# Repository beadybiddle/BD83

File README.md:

# BD83
A fully custom 83 Key mechanical keyboard designed around the way that I type. I intend to be able to say that this is truly a keyboard customized to my liking.
The original motivation behind this project was just a frustration at standard ANSI layouts. This project features custom everything, including PCB, plate, case, firmware, and eventually keycaps. Before creating anything, I initially just filmed my hands typing and gaming for an hour to figure out my own tendencies and key usage.

### Layout changes:
- Space bar is shrunk and split because nobody needs six keys' worth of real estate to hit one button.
- Backspace is shrunk because I don't intend to use it there. I've added a secondary backspace between the space bars.
- Caps lock is useless. I've removed it.
- Right shift is useless. I've removed it.
- Numpad function is incorporated into the FN layer on the lefthand side.
- Nav cluster has been moved around the arrow keys so it's easier and more intuitive to navigate code with home/end.
- F13 is now a thing because I had room for it.

### Hardware
There are three main custom hardware components to this keyboard:
- PCB, self explanatory
- Plate, the layer that the keyswitches clip into
- Case, the pieces that house the rest of the board

#### Plate
Keyboards don't necessarily need a plate, but for a myriad of reasons it made sense for me to use one. The plate is 0.06" 304 stainless steel, making it unyielding which is better for linear switch typefeel. I generated a template in swillKB then modeled the plate in Fusion360. Using the DXF exported from Fusion, I waterjet cut the plate.

#### Case
I've designed two cases, one which is full-sized and intended to be printed on a Form 3L SLA printer at the GaTech Invention Studio, and another which is minimal (hardly qualifying as a case) that I printed on my Voxelab Aquila. All outward-facing edges are chamfered or filleted to look nice and not hurt the flesh. On the back is a hole for a USB-C adapter dongle to poke through. The underside features a pretty beadybiddle logo and some rubber feet made from EPDM rubber bands. I also designed a wrist rest to be extra, but I've made the case so slim that it's not necessary.
I was unable to get access to the Form 3L before the studio closed for the year.

The two halves of the case are fastened by eight M3x10 machine screws and nuts around the perimeter. The plate has flanges around the edges that allow it to be sandwiched between these two halves, cushioned by strips of EPDM to dampen the sound and make the typefeel just a little springy. The interior of the case has only 0.8mm of wiggle room to the dangling PCB, making it literally as compact as possible. It is angled five degrees so that the front height is minimized while making room for the Feather board and batteries in the back.

The minimal "case" is actually four feet that clip onto the plate and are secured by a single large band. It has the same five degree inclination as the full case so that the electronics won't touch the desk surface. The open design leaves the switches and PCB accessible.

#### PCB
The PCB took the longest of all the components (maybe because I'd never made one before) but I'll try to keep it brief here:
I made it to support three main features: bluetooth, RGB lighting, and some level of expandability.
The brains of the board is an Adafruit Feather 32u4 Bluefruit LE, which is a devboard with an intregated nRF51822 BLE module. It also handles LiPo power for going completely wireless.
The LEDs are common-anode RGB packages, and are controlled by two IS31FL3733B drivers. The MCU talks to these drivers via I2C. I was originally planning to use a string of WS2812Bs or SK6812Es, but these have a substantially higher power draw than the ISSI scanning matrix drivers.
There are only 20 GPIO pins on the Feather, though, and several are already used for SPI with the BLE module. In order to accomodate my ideal 83 keys, it would take at least 19 pins to connect all the switches even with matrix duplexing, a number that I couldn't muster while dedicating three to the LED drivers. To get get some extra GPIO, I use an MCP23017 I2C I/O expander. This communicates on the same I2C lines as the ISSI drivers, and creates an additional 16 GPIO pins - more than enough for the rest of the switch matrix.

Diodes are placed between each switch and its corresponding row to prevent ghosting as the matrix is scanned.
VCC is fed through decoupling caps as needed to the slave chips; decoupling around the MCU is already handled by the Feather board.
The address pins on the three I2C chips have solder bridges for customizing the addresses if more devices are added.
A SPDT switch controls the 3V3 regulator enable pin so that power can be controlled, especially when going wireless.

The PCB was definitely the most fun part of this whole project; learning to make something so different from what I'm used to was nice.
I routed all of the traces twice because after getting an understanding and making some messy paths the first time it was much easier to organize the rats nest from scratch.
I also went through several iterations of component placements in the process in order to make room for the traces and switches. Most keyboards have plenty of free real estate behind their big spacebars or above the arrow keys, but my compact layout meant everything had to be crammed in tight gaps.

This was also the first time I'd done reflow soldering, but that was easy enough with the stencil and oven. And only one diode was backwards!

Designed in KiCad and fabricated by JLCPCB.

### Firmware
Easily the most difficult (or maybe just frustrating?) part, I wrote custom firmware for the board with the help of the QMK framework. QMK handles a lot of the nitty gritty stuff so that I instead dedicate dozens of hours to custom matrix scanning and debugging the RGB.
Defining switch order, keymappings, and LED positions was tedious but simple. The real problem was that as far as I can tell, I'm the first person to make a keyboard that drives rows from the MCU and read columns from an IO expander.
I visited square one a few times, rewriting the firmware each time I ran into a deadend that couldn't be debugged.
The first time, I thought the board wasn't flashing. Turns out it was flashing, but the firmware I wrote sucked so bad that it kicked back into bootloader.
The second time, I had it flashed but nothing responded and no debug messages even printed. I never figured out why, because I just rewrote everything after a day of failed debugging.
Finally I have the (mostly) working firmware, which is fully functional as a keyboard input and also supports typing over bluetooth. Unfortunately the RGB still doesn't work for some unknown reason, but luckily the BLE meets the critera for additional features to the keyboard.

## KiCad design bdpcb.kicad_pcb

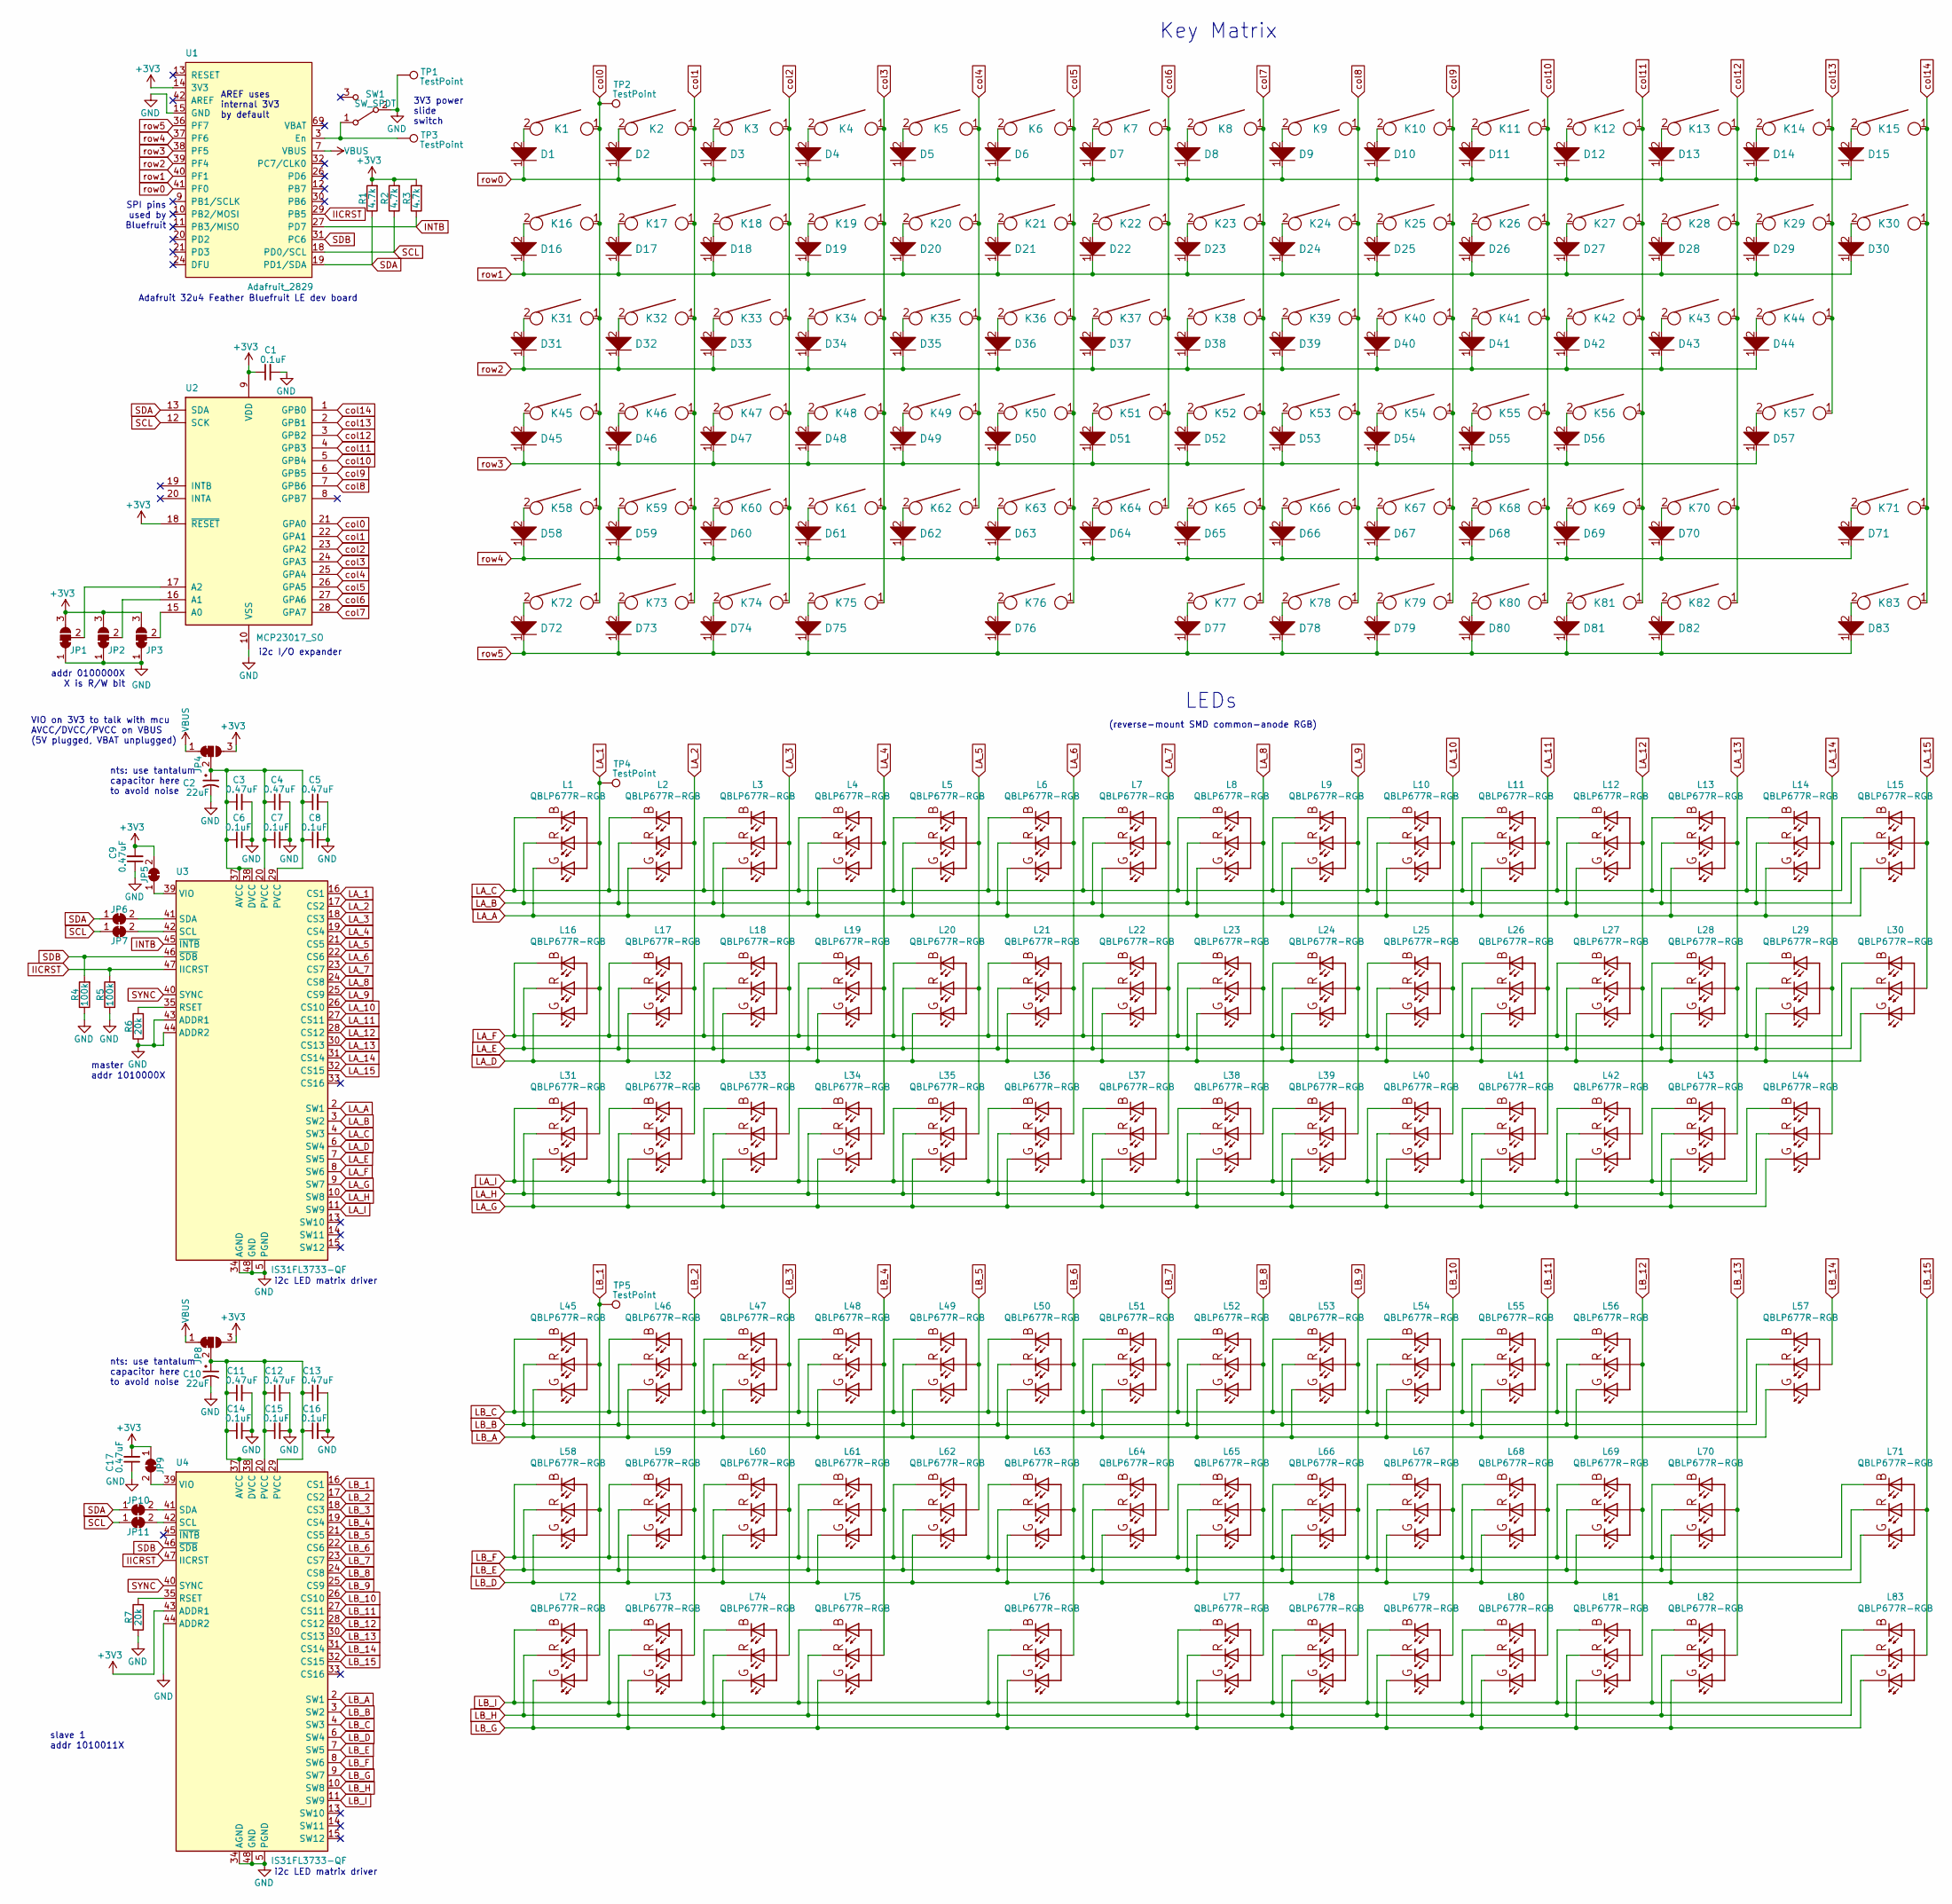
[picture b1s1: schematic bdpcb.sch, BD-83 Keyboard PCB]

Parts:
C1, C6, C7, C8, C14, C15, C16: 0.1uF; C_0805_2012Metric
C2, C10: 22uF; C_0805_2012Metric
C3, C4, C5, C9, C11, C12, C13, C17: 0.47uF; C_0805_2012Metric
D1, D2, D3, D4, D5, D6, D7, D8, D9, D10, D11, D12, D13, D14, D15, D16, D17, D18, D19, D20, D21, D22, D23, D24, D25, D26, D27, D28, D29, D30, D31, D32, D33, D34, D35, D36, D37, D38, D39, D40, D41, D42, D43, D44, D45, D46, D47, D48, D49, D50, D51, D52, D53, D54, D55, D56, D57, D58, D59, D60, D61, D62, D63, D64, D65, D66, D67, D68, D69, D70, D71, D72, D73, D74, D75, D76, D77, D78, D79, D80, D81, D82, D83: D; D_SOD-123
JP1, JP2, JP3, JP4, JP8: 13_bridge; SolderJumper-3_P1.3mm_Bridged12_RoundedPad1.0x1.5mm
JP5, JP6, JP7, JP9, JP10, JP11: SolderJumper_2_Bridged; SolderJumper-2_P1.3mm_Bridged_RoundedPad1.0x1.5mm
K1, K2, K3, K4, K5, K6, K7, K8, K9, K10, K11, K12, K13, K14, K15, K16, K17, K18, K19, K20, K21, K22, K23, K24, K25, K26, K27, K28, K29, K30, K32, K33, K34, K35, K36, K37, K38, K39, K40, K41, K42, K43, K46, K47, K48, K49, K50, K51, K52, K53, K54, K55, K56, K59, K60, K61, K62, K63, K64, K65, K66, K67, K68, K69, K70, K71, K76, K78, K79, K80, K81, K82, K83: KEYSW; MXOnly-1U-NoLED
K31, K44: KEYSW; MXOnly-1.5U-NoLED
K45: KEYSW; MXOnly-1.75U-NoLED
K57: KEYSW; MXOnly-2.25U-NoLED
K58: KEYSW; MXOnly-2U-NoLED
K72, K73, K74: KEYSW; MXOnly-1.25U-NoLED
K75, K77: KEYSW; MXOnly-2U-ReversedStabilizers-NoLED
L1, L2, L3, L4, L5, L6, L7, L8, L9, L10, L11, L12, L13, L14, L15, L16, L17, L18, L19, L20, L21, L22, L23, L24, L25, L26, L27, L28, L29, L30, L31, L32, L33, L34, L35, L36, L37, L38, L39, L40, L41, L42, L43, L44, L45, L46, L47, L48, L49, L50, L51, L52, L53, L54, L55, L56, L57, L58, L59, L60, L61, L62, L63, L64, L65, L66, L67, L68, L69, L70, L71, L72, L73, L74, L75, L76, L77, L78, L79, L80, L81, L82, L83: QBLP677R-RGB; RGB-REVERSE_MOUNT
R1, R2, R3: 4.7k; R_0805_2012Metric
R4, R5: 100k; R_0805_2012Metric
R6, R7: 20k; R_0805_2012Metric
SW1: SW_SPDT; SW_SPDT_CK-JS102011SAQN
TP1, TP3: TestPoint; TestPoint_Plated_Hole_D2.0mm
TP2, TP4, TP5: TestPoint; TestPoint_Pad_D2.5mm
U1: Adafruit_2829; ADAFRUIT_2829
U2: MCP23017_SO; SOIC-28W_7.5x17.9mm_P1.27mm
U3, U4: IS31FL3733-QF; QFN-48-1EP_6x6mm_P0.4mm_EP4.2x4.2mm

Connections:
+3V3: C1.1, C9.2, C17.2, JP1.3 (B), JP2.3 (B), JP3.3 (B), JP4.3 (B), JP5.2 (B), JP8.3 (B), JP9.1 (A), R1.2, R2.2, R3.2, U1.14 (3V3), U2.9 (VDD), U2.18 (~RESET~), U4.43 (ADDR1); also elsewhere on the board
GND: C1.2, C2.2, C3.2, C4.2, C5.2, C6.2, C7.2, C8.2, C9.1, C10.2, C11.2, C12.2, C13.2, C14.2, C15.2, C16.2, C17.1, JP1.1 (A), JP2.1 (A), JP3.1 (A), R4.1, R5.1, R6.1, R7.1, SW1.2 (B), TP1.1, U1.15 (GND), U2.10 (VSS), U3.5 (PGND), U3.12 (PGND), U3.34 (AGND), U3.43 (ADDR1), U3.44 (ADDR2), U3.48 (GND), U3.49 (GND), U4.5 (PGND), U4.12 (PGND), U4.34 (AGND), U4.44 (ADDR2), U4.48 (GND), U4.49 (GND)
IICRST: R5.2, U1.29 (PB5), U3.47 (IICRST), U4.47 (IICRST)
INTB: R3.1, U1.27 (PD7), U3.45 (~INTB)
LA_1: L1.COMMON_ANODE, L16.COMMON_ANODE, L31.COMMON_ANODE, TP4.1, U3.16 (CS1)
LA_2: L2.COMMON_ANODE, L17.COMMON_ANODE, L32.COMMON_ANODE, U3.17 (CS2)
LA_3: L3.COMMON_ANODE, L18.COMMON_ANODE, L33.COMMON_ANODE, U3.18 (CS3)
LA_4: L4.COMMON_ANODE, L19.COMMON_ANODE, L34.COMMON_ANODE, U3.19 (CS4)
LA_5: L5.COMMON_ANODE, L20.COMMON_ANODE, L35.COMMON_ANODE, U3.21 (CS5)
LA_6: L6.COMMON_ANODE, L21.COMMON_ANODE, L36.COMMON_ANODE, U3.22 (CS6)
LA_7: L7.COMMON_ANODE, L22.COMMON_ANODE, L37.COMMON_ANODE, U3.23 (CS7)
LA_8: L8.COMMON_ANODE, L23.COMMON_ANODE, L38.COMMON_ANODE, U3.24 (CS8)
LA_9: L9.COMMON_ANODE, L24.COMMON_ANODE, L39.COMMON_ANODE, U3.25 (CS9)
LA_10: L10.COMMON_ANODE, L25.COMMON_ANODE, L40.COMMON_ANODE, U3.26 (CS10)
LA_11: L11.COMMON_ANODE, L26.COMMON_ANODE, L41.COMMON_ANODE, U3.27 (CS11)
LA_12: L12.COMMON_ANODE, L27.COMMON_ANODE, L42.COMMON_ANODE, U3.28 (CS12)
LA_13: L13.COMMON_ANODE, L28.COMMON_ANODE, L43.COMMON_ANODE, U3.30 (CS13)
LA_14: L14.COMMON_ANODE, L29.COMMON_ANODE, L44.COMMON_ANODE, U3.31 (CS14)
LA_15: L15.COMMON_ANODE, L30.COMMON_ANODE, U3.32 (CS15)
LA_A: L1.2, L2.2, L3.2, L4.2, L5.2, L6.2, L7.2, L8.2, L9.2, L10.2, L11.2, L12.2, L13.2, L14.2, L15.2, U3.2 (SW1)
LA_B: L1.3, L2.3, L3.3, L4.3, L5.3, L6.3, L7.3, L8.3, L9.3, L10.3, L11.3, L12.3, L13.3, L14.3, L15.3, U3.3 (SW2)
LA_C: L1.1, L2.1, L3.1, L4.1, L5.1, L6.1, L7.1, L8.1, L9.1, L10.1, L11.1, L12.1, L13.1, L14.1, L15.1, U3.4 (SW3)
LA_D: L16.2, L17.2, L18.2, L19.2, L20.2, L21.2, L22.2, L23.2, L24.2, L25.2, L26.2, L27.2, L28.2, L29.2, L30.2, U3.6 (SW4)
LA_E: L16.3, L17.3, L18.3, L19.3, L20.3, L21.3, L22.3, L23.3, L24.3, L25.3, L26.3, L27.3, L28.3, L29.3, L30.3, U3.7 (SW5)
LA_F: L16.1, L17.1, L18.1, L19.1, L20.1, L21.1, L22.1, L23.1, L24.1, L25.1, L26.1, L27.1, L28.1, L29.1, L30.1, U3.8 (SW6)
LA_G: L31.2, L32.2, L33.2, L34.2, L35.2, L36.2, L37.2, L38.2, L39.2, L40.2, L41.2, L42.2, L43.2, L44.2, U3.9 (SW7)
LA_H: L31.3, L32.3, L33.3, L34.3, L35.3, L36.3, L37.3, L38.3, L39.3, L40.3, L41.3, L42.3, L43.3, L44.3, U3.10 (SW8)
LA_I: L31.1, L32.1, L33.1, L34.1, L35.1, L36.1, L37.1, L38.1, L39.1, L40.1, L41.1, L42.1, L43.1, L44.1, U3.11 (SW9)
LB_1: L45.COMMON_ANODE, L58.COMMON_ANODE, L72.COMMON_ANODE, TP5.1, U4.16 (CS1)
LB_2: L46.COMMON_ANODE, L59.COMMON_ANODE, L73.COMMON_ANODE, U4.17 (CS2)
LB_3: L47.COMMON_ANODE, L60.COMMON_ANODE, L74.COMMON_ANODE, U4.18 (CS3)
LB_4: L48.COMMON_ANODE, L61.COMMON_ANODE, L75.COMMON_ANODE, U4.19 (CS4)
LB_5: L49.COMMON_ANODE, L62.COMMON_ANODE, U4.21 (CS5)
LB_6: L50.COMMON_ANODE, L63.COMMON_ANODE, L76.COMMON_ANODE, U4.22 (CS6)
LB_7: L51.COMMON_ANODE, L64.COMMON_ANODE, U4.23 (CS7)
LB_8: L52.COMMON_ANODE, L65.COMMON_ANODE, L77.COMMON_ANODE, U4.24 (CS8)
LB_9: L53.COMMON_ANODE, L66.COMMON_ANODE, L78.COMMON_ANODE, U4.25 (CS9)
LB_10: L54.COMMON_ANODE, L67.COMMON_ANODE, L79.COMMON_ANODE, U4.26 (CS10)
LB_11: L55.COMMON_ANODE, L68.COMMON_ANODE, L80.COMMON_ANODE, U4.27 (CS11)
LB_12: L56.COMMON_ANODE, L69.COMMON_ANODE, L81.COMMON_ANODE, U4.28 (CS12)
LB_13: L70.COMMON_ANODE, L82.COMMON_ANODE, U4.30 (CS13)
LB_14: L57.COMMON_ANODE, U4.31 (CS14)
LB_15: L71.COMMON_ANODE, L83.COMMON_ANODE, U4.32 (CS15)
LB_A: L45.2, L46.2, L47.2, L48.2, L49.2, L50.2, L51.2, L52.2, L53.2, L54.2, L55.2, L56.2, L57.2, U4.2 (SW1)
LB_B: L45.3, L46.3, L47.3, L48.3, L49.3, L50.3, L51.3, L52.3, L53.3, L54.3, L55.3, L56.3, L57.3, U4.3 (SW2)
LB_C: L45.1, L46.1, L47.1, L48.1, L49.1, L50.1, L51.1, L52.1, L53.1, L54.1, L55.1, L56.1, L57.1, U4.4 (SW3)
LB_D: L58.2, L59.2, L60.2, L61.2, L62.2, L63.2, L64.2, L65.2, L66.2, L67.2, L68.2, L69.2, L70.2, L71.2, U4.6 (SW4)
LB_E: L58.3, L59.3, L60.3, L61.3, L62.3, L63.3, L64.3, L65.3, L66.3, L67.3, L68.3, L69.3, L70.3, L71.3, U4.7 (SW5)
LB_F: L58.1, L59.1, L60.1, L61.1, L62.1, L63.1, L64.1, L65.1, L66.1, L67.1, L68.1, L69.1, L70.1, L71.1, U4.8 (SW6)
LB_G: L72.2, L73.2, L74.2, L75.2, L76.2, L77.2, L78.2, L79.2, L80.2, L81.2, L82.2, L83.2, U4.9 (SW7)
LB_H: L72.3, L73.3, L74.3, L75.3, L76.3, L77.3, L78.3, L79.3, L80.3, L81.3, L82.3, L83.3, U4.10 (SW8)
LB_I: L72.1, L73.1, L74.1, L75.1, L76.1, L77.1, L78.1, L79.1, L80.1, L81.1, L82.1, L83.1, U4.11 (SW9)
unnamed 52: C2.1, C3.1, C4.1, C5.1, C6.1, C7.1, C8.1, JP4.2 (C), U3.20 (PVCC), U3.29 (PVCC), U3.37 (AVCC), U3.38 (DVCC); also elsewhere on the board
unnamed 53: C10.1, C11.1, C12.1, C13.1, C14.1, C15.1, C16.1, JP8.2 (C), U4.20 (PVCC), U4.29 (PVCC), U4.37 (AVCC), U4.38 (DVCC); also elsewhere on the board
unnamed: D1.2, K1.2
unnamed: D2.2, K2.2
unnamed: D3.2, K3.2
unnamed: D4.2, K4.2
unnamed: D5.2, K5.2
unnamed: D6.2, K6.2
unnamed: D7.2, K7.2
unnamed: D8.2, K8.2
unnamed: D9.2, K9.2
unnamed: D10.2, K10.2
unnamed: D11.2, K11.2
unnamed: D12.2, K12.2
unnamed: D13.2, K13.2
unnamed: D14.2, K14.2
unnamed: D15.2, K15.2
unnamed: D16.2, K16.2
unnamed: D17.2, K17.2
unnamed: D18.2, K18.2
unnamed: D19.2, K19.2
unnamed: D20.2, K20.2
unnamed: D21.2, K21.2
unnamed: D22.2, K22.2
unnamed: D23.2, K23.2
unnamed: D24.2, K24.2
unnamed: D25.2, K25.2
unnamed: D26.2, K26.2
unnamed: D27.2, K27.2
unnamed: D28.2, K28.2
unnamed: D29.2, K29.2
unnamed: D30.2, K30.2
unnamed: D31.2, K31.2
unnamed: D32.2, K32.2
unnamed: D33.2, K33.2
unnamed: D34.2, K34.2
unnamed: D35.2, K35.2
unnamed: D36.2, K36.2
unnamed: D37.2, K37.2
unnamed: D38.2, K38.2
unnamed: D39.2, K39.2
unnamed: D40.2, K40.2
unnamed: D41.2, K41.2
unnamed: D42.2, K42.2
unnamed: D43.2, K43.2
unnamed: D44.2, K44.2
unnamed: D45.2, K45.2
unnamed: D46.2, K46.2
unnamed: D47.2, K47.2
unnamed: D48.2, K48.2
unnamed: D49.2, K49.2
unnamed: D50.2, K50.2
unnamed: D51.2, K51.2
unnamed: D52.2, K52.2
unnamed: D53.2, K53.2
unnamed: D54.2, K54.2
unnamed: D55.2, K55.2
unnamed: D56.2, K56.2
unnamed: D57.2, K57.2
unnamed: D58.2, K58.2
unnamed: D59.2, K59.2
unnamed: D60.2, K60.2
unnamed: D61.2, K61.2
unnamed: D62.2, K62.2
unnamed: D63.2, K63.2
unnamed: D64.2, K64.2
unnamed: D65.2, K65.2
unnamed: D66.2, K66.2
unnamed: D67.2, K67.2
unnamed: D68.2, K68.2
unnamed: D69.2, K69.2
unnamed: D70.2, K70.2
unnamed: D71.2, K71.2
unnamed: D72.2, K72.2
unnamed: D73.2, K73.2
unnamed: D74.2, K74.2
unnamed: D75.2, K75.2
unnamed: D76.2, K76.2
unnamed: D77.2, K77.2
unnamed: D78.2, K78.2
unnamed: D79.2, K79.2
unnamed: D80.2, K80.2
unnamed: D81.2, K81.2
unnamed: D82.2, K82.2
unnamed: D83.2, K83.2
unnamed: JP1.2 (C), U2.17 (A2)
unnamed: JP2.2 (C), U2.16 (A1)
unnamed: JP3.2 (C), U2.15 (A0)
unnamed 140: JP5.1 (A), U3.39 (VIO); also elsewhere on the board
unnamed 141: JP6.2 (B), U3.41 (SDA); also elsewhere on the board
unnamed 142: JP7.2 (B), U3.42 (SCL); also elsewhere on the board
unnamed 143: JP9.2 (B), U4.39 (VIO); also elsewhere on the board
unnamed 144: JP10.2 (B), U4.41 (SDA); also elsewhere on the board
unnamed 145: JP11.2 (B), U4.42 (SCL); also elsewhere on the board
unnamed: R6.2, U3.35 (RSET)
unnamed: R7.2, U4.35 (RSET)
unnamed: SW1.1 (A), TP3.1, U1.3 (En)
SCL: JP7.1 (A), JP11.1 (A), R2.1, U1.18 (PD0/SCL), U2.12 (SCK); also elsewhere on the board
SDA: JP6.1 (A), JP10.1 (A), R1.1, U1.19 (PD1/SDA), U2.13 (SDA); also elsewhere on the board
SDB: R4.2, U1.31 (PC6), U3.46 (~SDB), U4.46 (~SDB)
SYNC: U3.40 (SYNC), U4.40 (SYNC)
VBUS: JP4.1 (A), JP8.1 (A), U1.7 (VBUS); also elsewhere on the board
col0: K1.1, K16.1, K31.1, K45.1, K58.1, K72.1, TP2.1, U2.21 (GPA0)
col1: K2.1, K17.1, K32.1, K46.1, K59.1, K73.1, U2.22 (GPA1)
col2: K3.1, K18.1, K33.1, K47.1, K60.1, K74.1, U2.23 (GPA2)
col3: K4.1, K19.1, K34.1, K48.1, K61.1, K75.1, U2.24 (GPA3)
col4: K5.1, K20.1, K35.1, K49.1, K62.1, U2.25 (GPA4)
col5: K6.1, K21.1, K36.1, K50.1, K63.1, K76.1, U2.26 (GPA5)
col6: K7.1, K22.1, K37.1, K51.1, K64.1, U2.27 (GPA6)
col7: K8.1, K23.1, K38.1, K52.1, K65.1, K77.1, U2.28 (GPA7)
col8: K9.1, K24.1, K39.1, K53.1, K66.1, K78.1, U2.7 (GPB6)
col9: K10.1, K25.1, K40.1, K54.1, K67.1, K79.1, U2.6 (GPB5)
col10: K11.1, K26.1, K41.1, K55.1, K68.1, K80.1, U2.5 (GPB4)
col11: K12.1, K27.1, K42.1, K56.1, K69.1, K81.1, U2.4 (GPB3)
col12: K13.1, K28.1, K43.1, K70.1, K82.1, U2.3 (GPB2)
col13: K14.1, K29.1, K44.1, K57.1, U2.2 (GPB1)
col14: K15.1, K30.1, K71.1, K83.1, U2.1 (GPB0)
row0: D1.1, D2.1, D3.1, D4.1, D5.1, D6.1, D7.1, D8.1, D9.1, D10.1, D11.1, D12.1, D13.1, D14.1, D15.1, U1.41 (PF0)
row1: D16.1, D17.1, D18.1, D19.1, D20.1, D21.1, D22.1, D23.1, D24.1, D25.1, D26.1, D27.1, D28.1, D29.1, D30.1, U1.40 (PF1)
row2: D31.1, D32.1, D33.1, D34.1, D35.1, D36.1, D37.1, D38.1, D39.1, D40.1, D41.1, D42.1, D43.1, D44.1, U1.39 (PF4)
row3: D45.1, D46.1, D47.1, D48.1, D49.1, D50.1, D51.1, D52.1, D53.1, D54.1, D55.1, D56.1, D57.1, U1.38 (PF5)
row4: D58.1, D59.1, D60.1, D61.1, D62.1, D63.1, D64.1, D65.1, D66.1, D67.1, D68.1, D69.1, D70.1, D71.1, U1.37 (PF6)
row5: D72.1, D73.1, D74.1, D75.1, D76.1, D77.1, D78.1, D79.1, D80.1, D81.1, D82.1, D83.1, U1.36 (PF7)

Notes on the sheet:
LEDs
Key Matrix
nts: use tantalum capacitor here to avoid noise
slave 1 addr 1010011X
master addr 1010000X
3V3 power slide switch
AREF uses internal 3V3 by default
addr 0100000X X is R/W bit
SPI pins used by Bluefruit
Adafruit 32u4 Feather Bluefruit LE dev board
i2c I/O expander
i2c LED matrix driver
(reverse-mount SMD common-anode RGB)
VIO on 3V3 to talk with mcu AVCC/DVCC/PVCC on VBUS (5V plugged, VBAT unplugged)

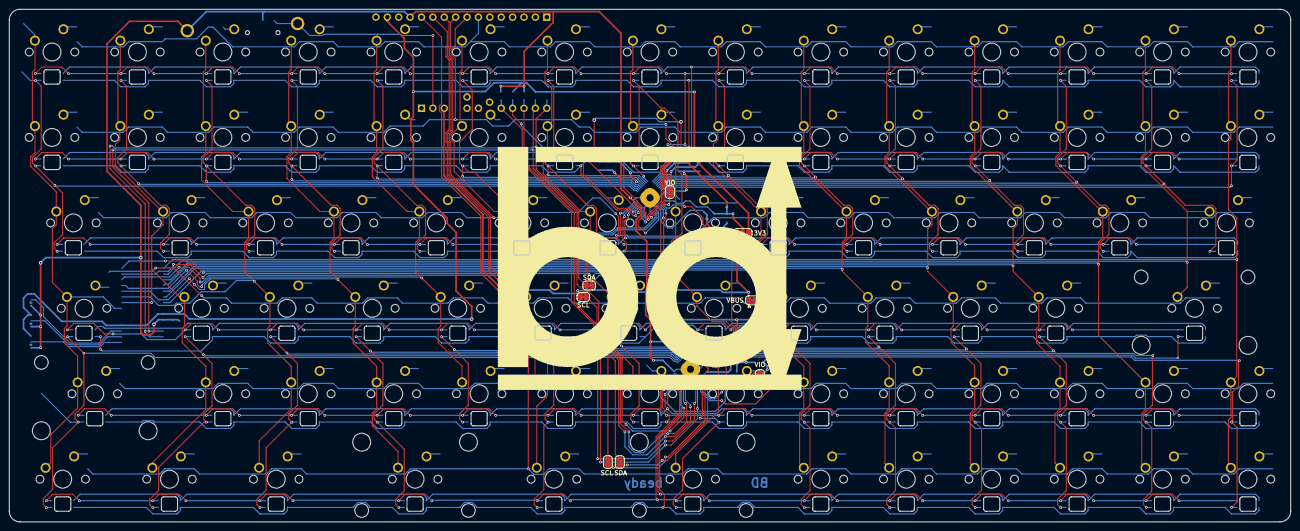
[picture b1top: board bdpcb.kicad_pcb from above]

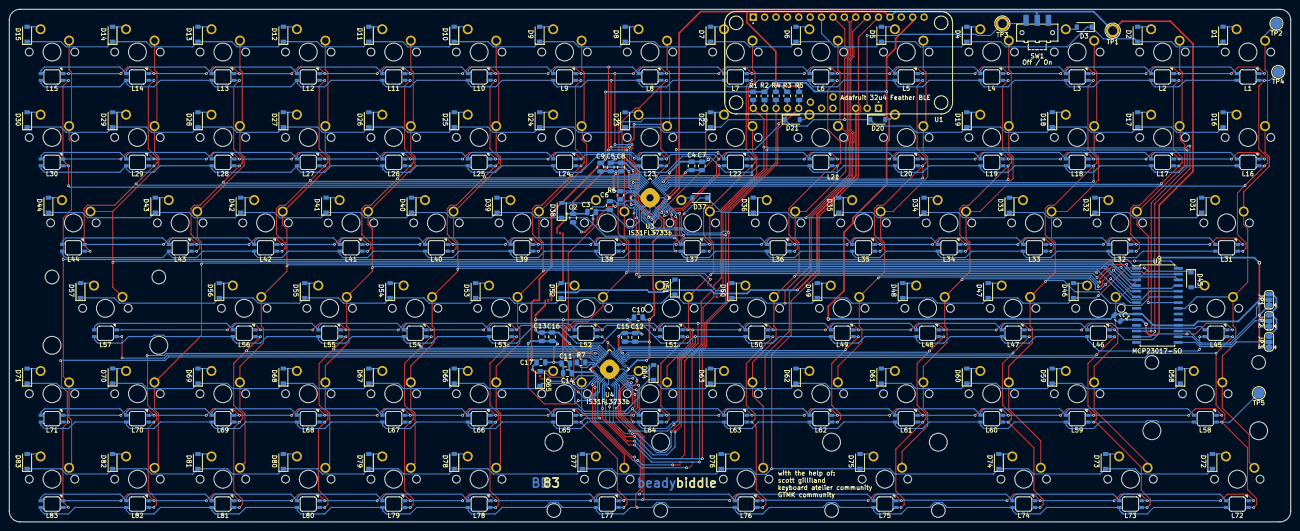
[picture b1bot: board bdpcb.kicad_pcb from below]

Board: 2 copper layers, 285.8 x 114.3 mm, 295 parts (203 on the bottom side), 175 nets.

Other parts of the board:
3V3: 13_bridge; SolderJumper-3_P1.3mm_Bridged12_RoundedPad1.0x1.5mm
G1: LOGO; BD_logo
SCL: SolderJumper_2_Bridged; SolderJumper-2_P1.3mm_Bridged_RoundedPad1.0x1.5mm
SCL#2: SolderJumper_2_Bridged; SolderJumper-2_P1.3mm_Bridged_RoundedPad1.0x1.5mm
SDA: SolderJumper_2_Bridged; SolderJumper-2_P1.3mm_Bridged_RoundedPad1.0x1.5mm
SDA#2: SolderJumper_2_Bridged; SolderJumper-2_P1.3mm_Bridged_RoundedPad1.0x1.5mm
VBUS: 13_bridge; SolderJumper-3_P1.3mm_Bridged12_RoundedPad1.0x1.5mm
VIO: SolderJumper_2_Bridged; SolderJumper-2_P1.3mm_Bridged_RoundedPad1.0x1.5mm
VIO#2: SolderJumper_2_Bridged; SolderJumper-2_P1.3mm_Bridged_RoundedPad1.0x1.5mm

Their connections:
+3V3: 3V3.3, VBUS.3, VIO.1, VIO#2.2; also elsewhere on the board
unnamed 52: 3V3.2; also elsewhere on the board
unnamed 53: VBUS.2; also elsewhere on the board
unnamed 140: VIO#2.1; also elsewhere on the board
unnamed 141: SDA#2.2; also elsewhere on the board
unnamed 142: SCL#2.2; also elsewhere on the board
unnamed 143: VIO.2; also elsewhere on the board
unnamed 144: SDA.2; also elsewhere on the board
unnamed 145: SCL.2; also elsewhere on the board
SCL: SCL.1, SCL#2.1; also elsewhere on the board
SDA: SDA.1, SDA#2.1; also elsewhere on the board
VBUS: 3V3.1, VBUS.1; also elsewhere on the board

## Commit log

2021-11-13 init
2021-11-14 removed mcu and BLE and power stuff
2021-11-14 IO expander not integrated yet
2021-11-18 scott's suggestions and new LED symbol/footprints
2021-11-18 starting pcb
2021-11-18 changed feather footprint and moving LEDS
2021-11-18 LEDs placed
2021-11-18 just diodes left to move, then fine tune and trace
2021-11-18 diodes roughly placed
2021-11-18 reverse stabs and outer edge cuts
2021-11-18 square LED cutouts
2021-11-18 beginning diode positioning
2021-11-18 rounded rectangle holes and starting diode traces
2021-11-18 two rows of diodes
2021-11-18 more diode routing
2021-11-19 good progress on traces
2021-11-19 getting there on traces
2021-11-19 schleeping
2021-11-19 fixed feather footprint pinout to match symbol
2021-11-19 bottom rows, still cant track to qfn pins
2021-11-19 random stuff; power switch, some cols, re-added accidentally deleted key
2021-11-19 readme skeleton
2021-11-19 tidied vertical traces and making superhighway
2021-11-19 doing LED cols
2021-11-20 tightening spacing on vias and traces, about to redo it all probs
2021-11-20 deleted all traces and vias
2021-11-21 reoriented diodes
2021-11-22 better row/col tracks starting
2021-11-22 almost there with row/col tracks
2021-11-22 idek
2021-11-23 4.7k i2c pullups and laying row tracks
2021-11-23 left half tracks down!
2021-11-23 rows and cols done
2021-11-23 added silkscreen hole on keysw pth front
2021-11-23 idk how im gonna get all these wires into these chips
2021-11-23 re-added feather VBUS pin7
2021-11-23 figured out how to change power track width
2021-11-23 added VBUS/3V3 bridges for driver power
2021-11-23 updated LED footprint
2021-11-23 removed led driver addr jumper bridges
2021-11-23 i/o expander routed
2021-11-23 reannotated and connected ic grounds
2021-11-24 two ICs down, one to go
2021-11-24 just caps and a jumper left
2021-11-24 everything routed!
2021-11-24 actually done with tracing now; DRC passes
2021-11-24 text sizing up to spec + new labels
2021-11-24 fancy author tag
2021-11-24 logo silkscreen
2021-11-24 thermal vias and fixed jumper silks
2021-11-24 driver thermal vias and gerber plot
2021-11-24 gerber folder
2021-11-24 drill files
2021-11-25 a lil background in the README
2021-11-25 just formatting and tidbits
2021-11-30 firmware folder
2021-11-30 groundwork for LEDs
2021-12-01 idk what im doing with LED and MCP i2c
2021-12-11 figuring out RGB framework from ktype
2021-12-11 led config layouts
2021-12-11 RGB config defines
2021-12-11 newer BLE support
2021-12-12 keymapping
2021-12-12 reset procedure
2021-12-12 custom scanning
2021-12-12 info layout
2021-12-12 successful compile after tweaks
2021-12-12 caterina bootloader
2021-12-12 closer to ferris
2021-12-12 disable RGB and BLE
2021-12-12 reduced further, flashes now but doesn't work
2021-12-12 re-adding RGB
2021-12-14 firmware redo; keyboard and BLE work now
2021-12-14 PEQL to EQL
2021-12-14 fixed RGB physical locations
2021-12-14 doc for CS3651
2021-12-14 images folder
2021-12-14 adding images
2021-12-14 one more image
2021-12-14 schema
2021-12-14 plate image
2021-12-14 reorg
2021-12-19 trying full RGB again
2021-12-19 cleaning config.h
2021-12-19 cleaning comments
2021-12-19 numlock and mycm mappings
2021-12-19 KC_NLCK keycode
2022-04-06 Set theme jekyll-theme-minimal
